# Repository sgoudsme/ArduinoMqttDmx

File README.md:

# ArduinoMqttDmx

Project for having an MQTT to DMX bridge.
This project is tested with the home assistant MQTT light.

This repository exists out of 2 parts: software implementation in Arduino and PCB drawing in KiCad

## Software
The software is written in Arduino. The serial registers are written directly.
The sofware can be found in the folder 'Arduino/Dmx'
Needed library:
 - pubsubclient

Before uploading this software, a serial number need to be uploaded in EEPROM. This way of programming gives every arduino a fixed number, without the constant need of changing the software. You can find the way of programming the serial number in my other repository: https://github.com/sgoudsme/Write-EEPROM-numbers.

Fill in the ip, username and password of your broker in the code. 

This bridge supports up to 50 DMX channels. Enlarging the buffer size is possible, but I had some unstabilities. 

The mqtt topic the arduino connects to is 'D0000/X/command' where D0000 will be overwritten with the serial number, found in the EEPROM and x the channel that need to be changed.

The payload of the MQTT messages should have the following structure:

{
  "state": ON,
  "brightness": 127,
  "transition": 5
}

with:
  state is ON or OFF,
  the brighness is a value between 0 and 255, 
  the transition is a value in seconds

## Hardware
The hardware drawing is made in Kicad V5. It simply contains a footprint for an arduino and a MAX485. Also some extra pins are exposed, when I would need some small button. This is not used for the moment. 
The MAX485 is connected to pin D1. 
A regular ethernetshield (W5100) is also needed for the MQTT part.

The plots are found in the folder "plots", and the PCB's are ordered at JLCPCB. 

At the moment of writing, the PCB's are in production, so I haven't tested them. The circuit is made on a breadboard and should be working.

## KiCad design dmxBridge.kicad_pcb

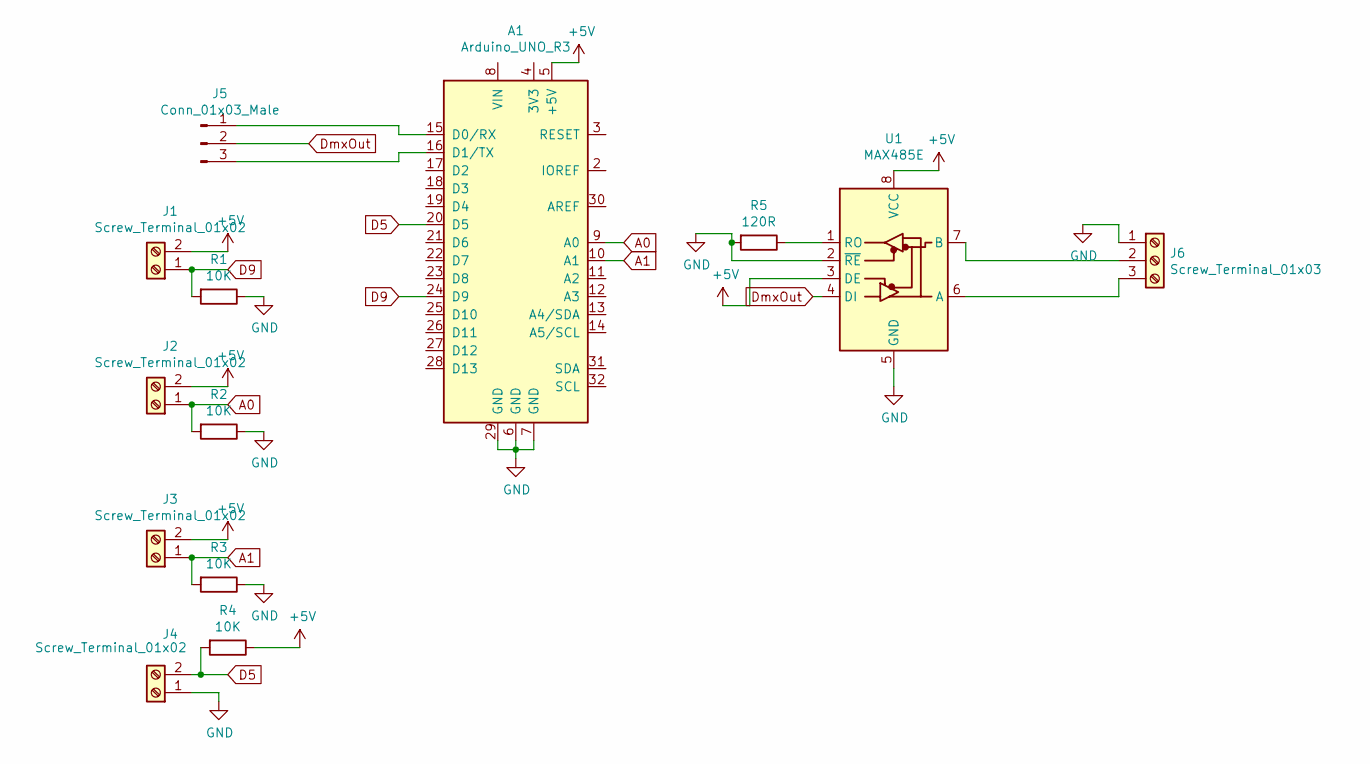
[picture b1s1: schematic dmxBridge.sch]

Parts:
A1: Arduino_UNO_R3
J1, J2, J3, J4: Screw_Terminal_01x02; TerminalBlock_bornier-2_P5.08mm
J5: Conn_01x03_Male; PinHeader_1x03_P2.54mm_Vertical
J6: Screw_Terminal_01x03; TerminalBlock_bornier-3_P5.08mm
R1, R2, R3, R4: 10K; R_0603_1608Metric_Pad1.05x0.95mm_HandSolder
R5: 120R; R_0603_1608Metric_Pad1.05x0.95mm_HandSolder
U1: MAX485E; SOIC-8_3.9x4.9mm_P1.27mm

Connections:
+5V: A1.5 (+5V), J1.2, J2.2, J3.2, R4.1, U1.3 (DE), U1.8 (VCC)
A0: A1.9 (A0), J2.1, R2.2
A1: A1.10 (A1), J3.1, R3.2
D5: A1.20 (D5), J4.2, R4.2
D9: A1.24 (D9), J1.1, R1.2
DmxOut: J5.2, U1.4 (DI)
GND: A1.6 (GND), A1.7 (GND), A1.29 (GND), J4.1, J6.1, R1.1, R2.1, R3.1, R5.2, U1.2 (~RE), U1.5 (GND)
unnamed: A1.15 (D0/RX), J5.1
unnamed: A1.16 (D1/TX), J5.3
unnamed: J6.2, U1.7 (B)
unnamed: J6.3, U1.6 (A)
unnamed: R5.1, U1.1 (RO)

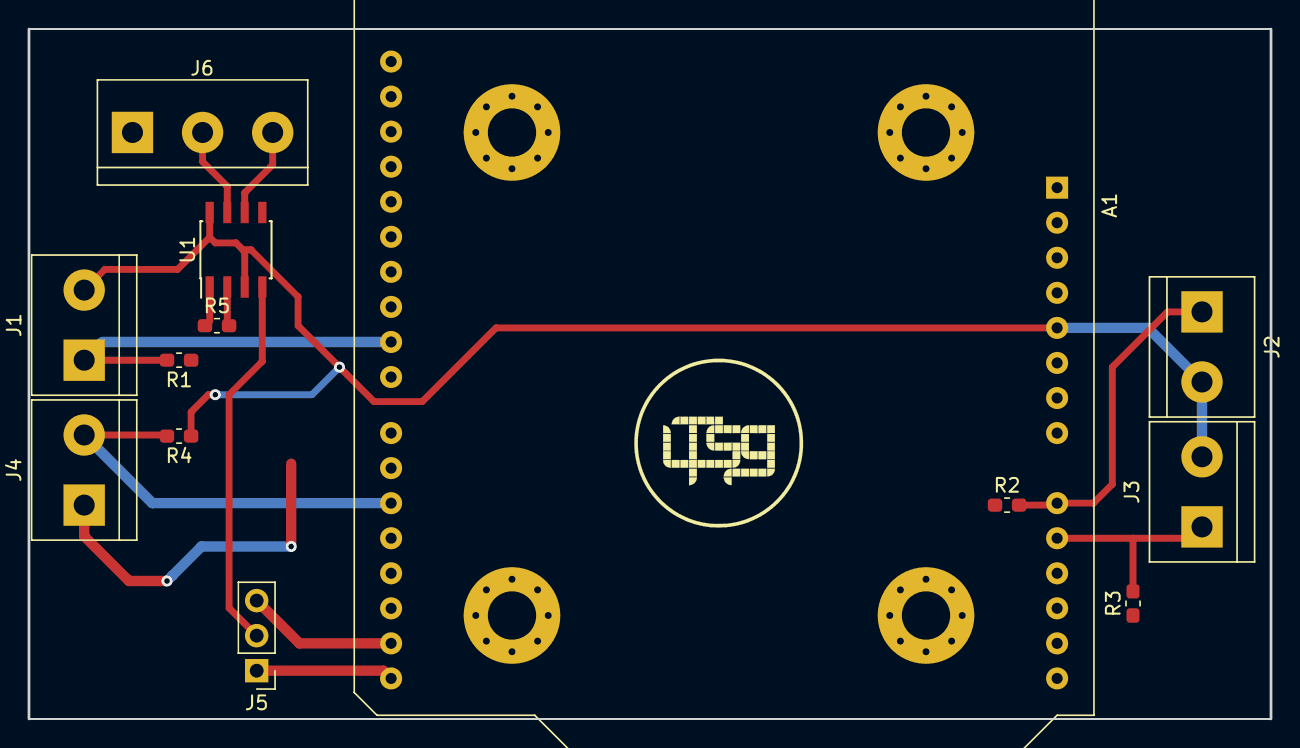
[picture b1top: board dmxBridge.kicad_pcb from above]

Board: 2 copper layers, 90.0 x 50.0 mm, 13 parts (0 on the bottom side), 12 nets.

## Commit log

2019-06-07 Add software implementation and explanation
2019-06-07 add KiCad drawings and explanation
2019-06-07 Update README.md
    add link to other repository for uploading the serial number
2019-06-08 add license file
2020-05-02 add debug statements
